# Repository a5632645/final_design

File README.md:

# final_design/毕业设计
This is my final design.  
这是我的本科毕业设计.  
> [!WARNING]
> don't try to rebuild hardware, it has too many incorrect design, that will just waste your time and money.  
> 请不要试着复刻硬件，有很多设计不合理的地方，复刻只会浪费你的时间和钱  

# digital waveguide synthesizer/数字波导合成器  
This is a MPE capability digital waveguide synthesizer.It has plucked, woodwind and bowed engine.Or you can use it as a MPE midi keyboard(only one octave).  
这是一个mpe兼容的数字波导合成器，有拨弦，木管和弓弦模型，也可以当成mpe键盘使用，尽管只有一个八度。  
# demo/演示
https://www.bilibili.com/video/BV1ghJGzJEi4/
# bug
硬件中含有较多问题  
the hardware has many bugs.

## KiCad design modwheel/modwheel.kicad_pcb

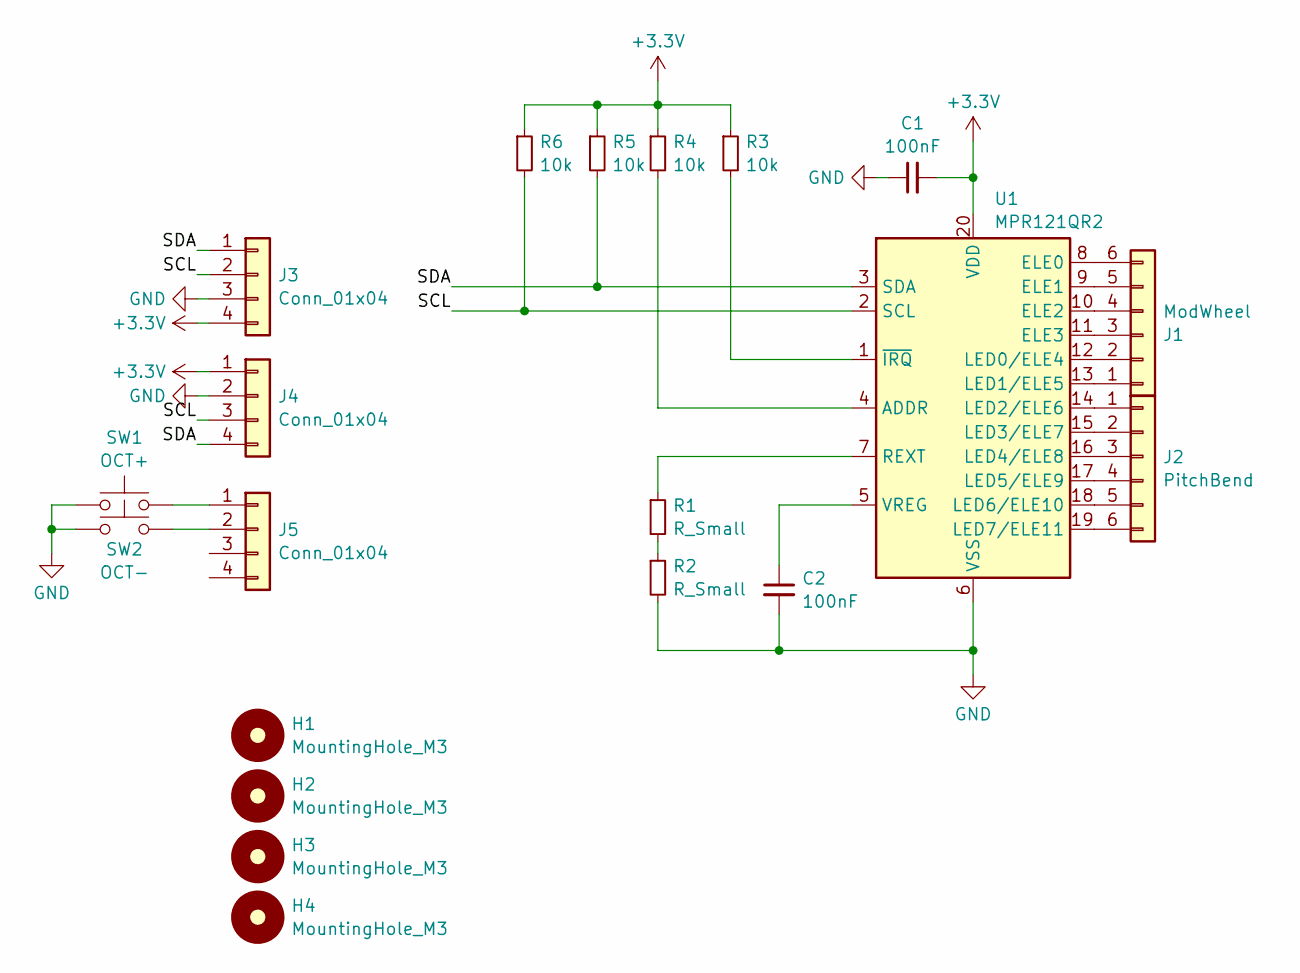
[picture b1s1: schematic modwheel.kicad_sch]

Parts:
C1, C2: 100nF; C_0603_1608Metric
H1, H2, H3, H4: MountingHole_M3; MountingHole_3.2mm_M3
J1: ModWheel; TouchSlider-6_50x10mm
J2: PitchBend; TouchSlider-6_50x10mm
J3, J4, J5: Conn_01x04; SM04BSRSSTB
R1, R2: R_Small; R_0603_1608Metric
R3, R4, R5, R6: 10k; R_0603_1608Metric
SW1: OCT+; KEY-SMD_2P-L6.0-W6.0-P6.00
SW2: OCT-; KEY-SMD_2P-L6.0-W6.0-P6.00
U1: MPR121QR2; UQFN-20_3x3mm_P0.4mm

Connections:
+3.3V: C1.2, J3.4, J4.1, R3.1, R4.1, R5.1, R6.1, U1.20 (VDD)
/SCL: J3.2, J4.3, R6.2, U1.2 (SCL)
/SDA: J3.1, J4.4, R5.2, U1.3 (SDA)
GND: C1.1, C2.2, J3.3, J4.2, R2.2, SW1.1, SW2.1, U1.6 (VSS)
unnamed: J1.1, U1.13 (LED1/ELE5)
unnamed: J1.2, U1.12 (LED0/ELE4)
unnamed: J1.3, U1.11 (ELE3)
unnamed: J1.4, U1.10 (ELE2)
unnamed: J1.5, U1.9 (ELE1)
unnamed: J1.6, U1.8 (ELE0)
unnamed: J2.1, U1.14 (LED2/ELE6)
unnamed: J2.2, U1.15 (LED3/ELE7)
unnamed: J2.3, U1.16 (LED4/ELE8)
unnamed: J2.4, U1.17 (LED5/ELE9)
unnamed: J2.5, U1.18 (LED6/ELE10)
unnamed: J2.6, U1.19 (LED7/ELE11)
unnamed: J5.1, SW1.2
unnamed: J5.2, SW2.2
unnamed: R1.2, R2.1
unnamed: R4.2, U1.4 (ADDR)
unnamed: R1.1, U1.7 (REXT)
unnamed: C2.1, U1.5 (VREG)
unnamed: R3.2, U1.1 (~IRQ)

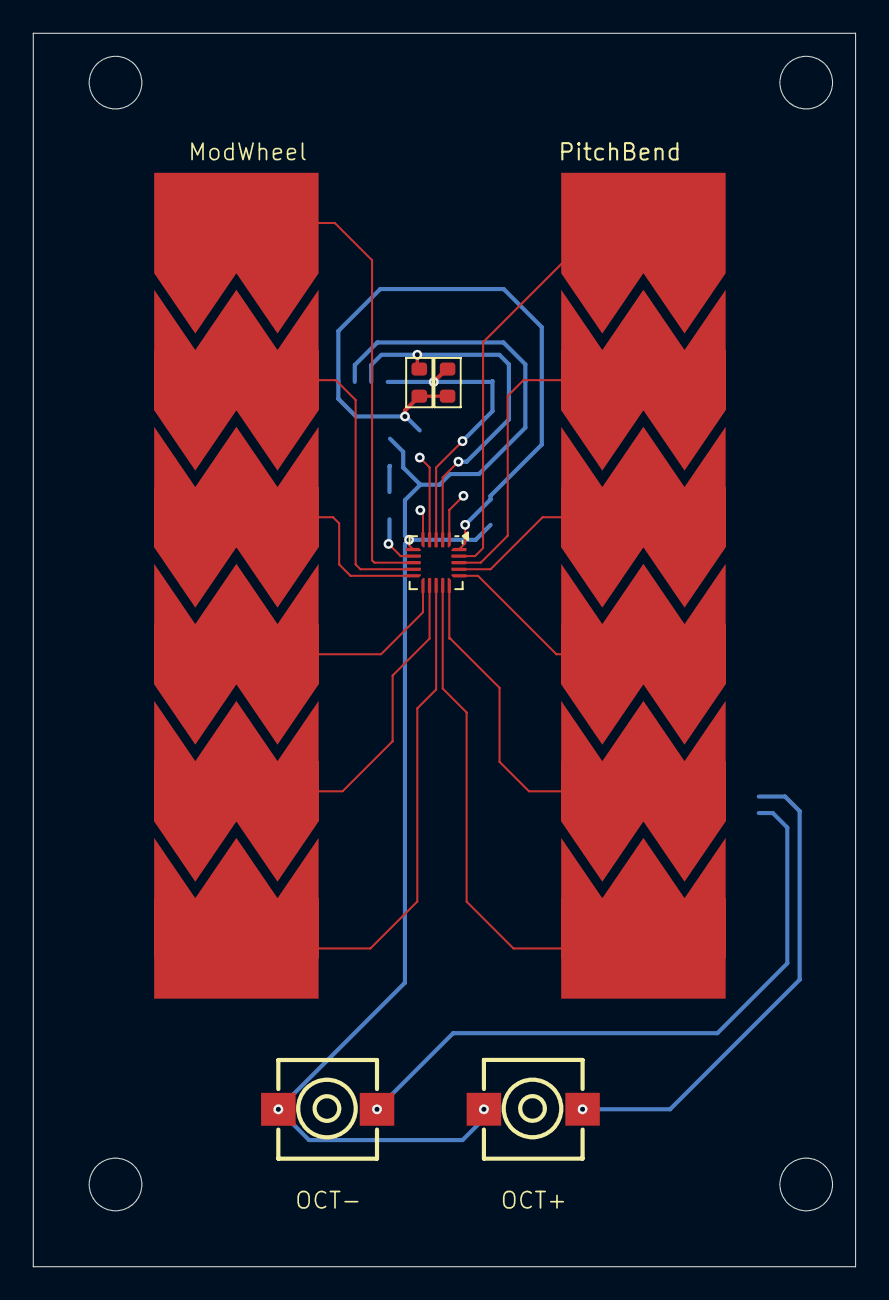
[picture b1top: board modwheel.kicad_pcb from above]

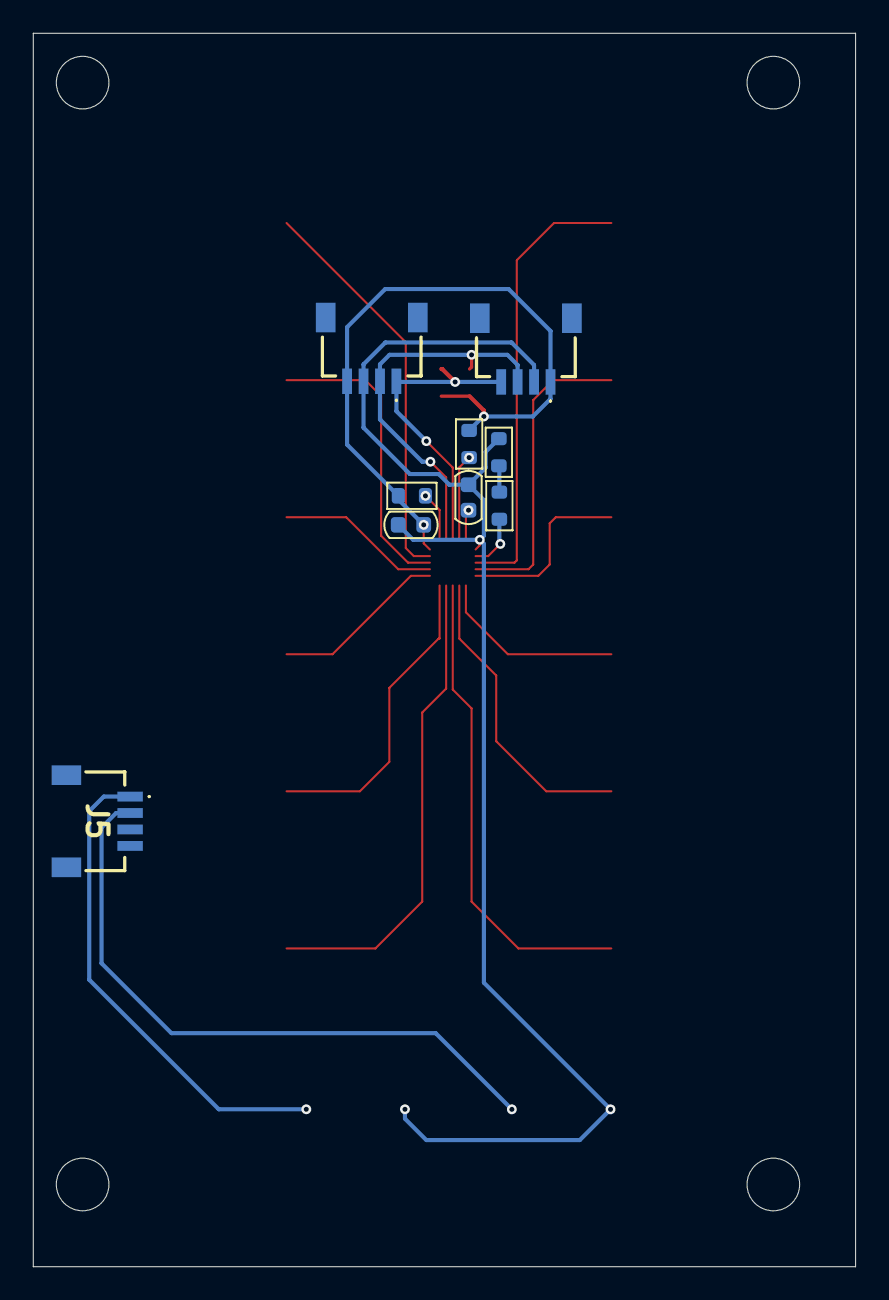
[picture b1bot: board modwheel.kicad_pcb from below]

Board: 2 copper layers, 50.0 x 75.0 mm, 20 parts (9 on the bottom side), 23 nets.

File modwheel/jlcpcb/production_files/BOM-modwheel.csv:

Comment,Designator,Footprint,LCSC,Quantity
Conn_01x04,J5,SM04BSRSSTB,,1
MPR121QR2,U1,UQFN-20_3x3mm_P0.4mm,,1
MountingHole_M3,H1,MountingHole_3.2mm_M3,,1
OCT+,SW1,KEY-SMD_2P-L6.0-W6.0-P6.00,,1
MountingHole_M3,H3,MountingHole_3.2mm_M3,,1
MountingHole_M3,H4,MountingHole_3.2mm_M3,,1
PitchBend,J2,TouchSlider-6_50x10mm,,1
ModWheel,J1,TouchSlider-6_50x10mm,,1
OCT-,SW2,KEY-SMD_2P-L6.0-W6.0-P6.00,,1
MountingHole_M3,H2,MountingHole_3.2mm_M3,,1
R_Small,R2,R_0603_1608Metric,,1
Conn_01x04,J3,SM04BSRSSTB,,1
R_Small,R1,R_0603_1608Metric,,1
100nF,C1,C_0603_1608Metric,,1
Conn_01x04,J4,SM04BSRSSTB,,1
100nF,C2,C_0603_1608Metric,,1
10k,R4,R_0603_1608Metric,,1
10k,R3,R_0603_1608Metric,,1
10k,R6,R_0603_1608Metric,,1
10k,R5,R_0603_1608Metric,,1

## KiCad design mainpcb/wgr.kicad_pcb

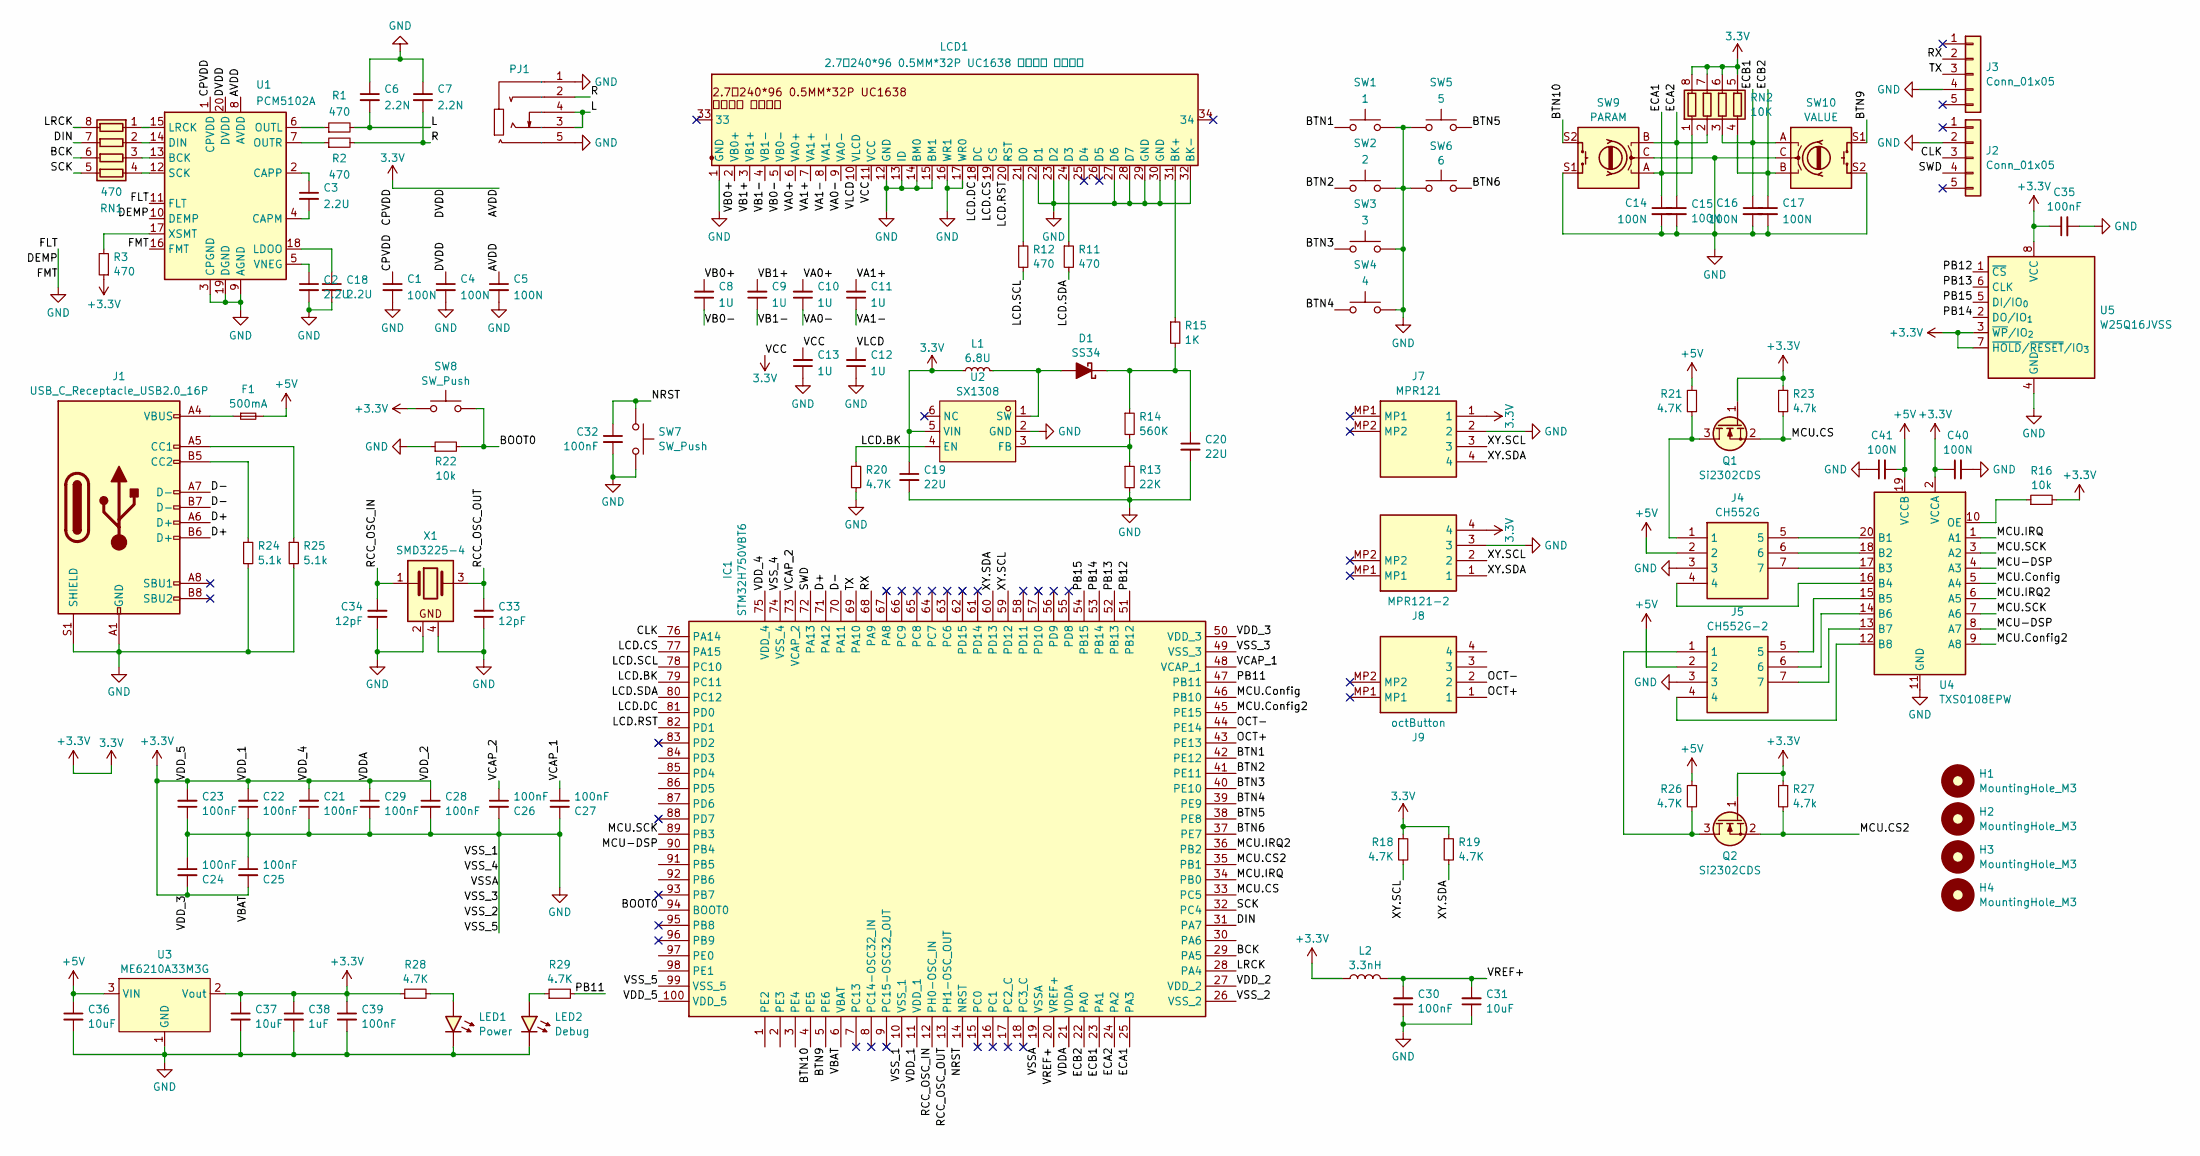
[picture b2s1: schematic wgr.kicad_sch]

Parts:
C1, C4, C5, C14, C15, C16, C17: 100N; C_0805_2012Metric
C2, C3, C18: 2.2U; C_0805_2012Metric
C6, C7: 2.2N; C_0805_2012Metric
C8, C9, C10, C11, C12, C13: 1U; C_0805_2012Metric
C19, C20: 22U; C_1206_3216Metric
C21, C22, C23, C24, C25, C26, C27, C28, C29, C30, C32, C35, C39: 100nF; C_0603_1608Metric
C31: 10uF; C_0603_1608Metric
C33, C34: 12pF; C_0603_1608Metric
C36, C37: 10uF; C_0805_2012Metric
C38: 1uF; C_0805_2012Metric
C40, C41: 100N; C_0603_1608Metric
D1: SS34; D_SMA
F1: 500mA; Fuse_0603_1608Metric
H1, H2, H3, H4: MountingHole_M3; MountingHole_3.2mm_M3
IC1: STM32H750VBT6; QFP50P1600X1600X160-100N; Manufacturer_Part_Number STM32H750VBT6; Mouser Part Number 511-STM32H750VBT6
J1: USB_C_Receptacle_USB2.0_16P; USB_C_Receptacle_G-Switch_GT-USB-7010ASV
J2, J3: Conn_01x05; Harwin_M20-89005xx_1x05_P2.54mm_Horizontal
J4: CH552G; SM07B-SRSS-TB; Manufacturer_Part_Number SM07B-SRSS-TB (LF)(SN)
J5: CH552G-2; SM07B-SRSS-TB; Manufacturer_Part_Number SM07B-SRSS-TB (LF)(SN)
J7: MPR121; SM04BSRSSTB; Manufacturer_Part_Number SM04B-SRSS-TB
J8: MPR121-2; SM04BSRSSTB; Manufacturer_Part_Number SM04B-SRSS-TB
J9: octButton; SM04BSRSSTB; Manufacturer_Part_Number SM04B-SRSS-TB
L1: 6.8U; L_APV_APH0420
L2: 3.3nH; L_0603_1608Metric; Part Number MI0603K300R-10
LCD1: 2.7寸240*96 0.5MM*32P UC1638 三串背光 背面插座; Hirose_FH12-32S-0.5SH_1x32-1MP_P0.50mm_Horizontal
LED1: Power; LED_0805_2012Metric
LED2: Debug; LED_0805_2012Metric
PJ1: AUDIO-IN-SMD_PJ-327A_C22355751; Manufacturer Part PJ-327A; LCSC Part Name PJ-327A
Q1, Q2: Si2302CDS; SOT-23
R1, R2, R3, R11, R12: 470; R_0805_2012Metric
R13: 22K; R_0603_1608Metric
R14: 560K; R_0603_1608Metric
R15: 1K; R_0805_2012Metric
R16: 10k; R_0603_1608Metric
R18, R19, R20, R21, R26, R28, R29: 4.7K; R_0805_2012Metric
R22: 10k; R_0603_1608Metric_Pad0.98x0.95mm
R23, R27: 4.7k; R_0805_2012Metric
R24, R25: 5.1k; R_0603_1608Metric_Pad0.98x0.95mm
RN1: 470; R_Array_Convex_4x0603
RN2: 10K; R_Array_Convex_4x0603
SW1: 1; KEY-SMD_2P-L6.0-W6.0-P6.00
SW2: 2; KEY-SMD_2P-L6.0-W6.0-P6.00
SW3: 3; KEY-SMD_2P-L6.0-W6.0-P6.00
SW4: 4; KEY-SMD_2P-L6.0-W6.0-P6.00
SW5: 5; KEY-SMD_2P-L6.0-W6.0-P6.00
SW6: 6; KEY-SMD_2P-L6.0-W6.0-P6.00
SW7, SW8: SW_Push; SW-SMD_4P-L4.5-W4.5-P3.00-LS7.0_TS-1009S-03826
SW9: PARAM; SW-TH_EC11XXXXXXXX
SW10: VALUE; SW-TH_EC11XXXXXXXX
U1: PCM5102A; TSSOP-20_4.4x6.5mm_P0.65mm
U2: SX1308; SOT-23-6_L2.9-W1.6-P0.95-LS2.8-BL; Manufacturer Part SX1308; LCSC Part Name 高效1.2MHz 2A升压转换器
U3: ME6210A33M3G; SOT-23
U4: TXS0108EPW; TSSOP-20_4.4x6.5mm_P0.65mm
U5: W25Q16JVSS; SOIC-8_5.3x5.3mm_P1.27mm
X1: SMD3225-4; Crystal_SMD_3225-4Pin_3.2x2.5mm

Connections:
+3.3V: C1.1, C4.1, C5.1, C13.2, C19.1, C21.2, C22.2, C23.2, C24.2, C25.2, C28.1, C29.1, C35.1, C37.1, C38.1, C39.1, C40.1, IC1.6 (VBAT), IC1.11 (VDD_1), IC1.21 (VDDA), IC1.27 (VDD_2), IC1.50 (VDD_3), IC1.75 (VDD_4), IC1.100 (VDD_5), J7.1, J8.4, L1.1, L2.1, LCD1.11 (VCC), Q1.1 (G), Q2.1 (G), R3.1, R16.2, R18.1, R19.1, R23.1, R27.1, R28.1, RN2.5 (R4.2), RN2.6 (R3.2), RN2.7 (R2.2), RN2.8 (R1.2), SW8.1, U1.1 (CPVDD), U1.8 (AVDD), U1.20 (DVDD), U2.5 (VIN), U3.2 (Vout), U4.2 (VCCA), U5.3 (~WP/IO_{2}), U5.7 (~HOLD/~RESET/IO_{3}), U5.8 (VCC)
+5V: C36.1, C41.2, F1.2, J4.2, J5.2, R21.1, R26.1, U3.3 (VIN), U4.19 (VCCB)
/BCK: IC1.29 (PA5), RN1.6 (R3.2)
/BOOT0: IC1.94 (BOOT0), R22.2, SW8.2
/BTN1: IC1.42 (PE12), SW1.1
/BTN2: IC1.41 (PE11), SW2.1
/BTN3: IC1.40 (PE10), SW3.1
/BTN4: IC1.39 (PE9), SW4.1
/BTN5: IC1.38 (PE8), SW5.2
/BTN6: IC1.37 (PE7), SW6.2
/BTN9: IC1.5 (PE6), SW10.S1
/BTN10: IC1.4 (PE5), SW9.S2
/CLK: IC1.76 (PA14), J2.3
/D+: IC1.71 (PA12), J1.A6 (D+), J1.B6 (D+)
/D-: IC1.70 (PA11), J1.A7 (D-), J1.B7 (D-)
/DIN: IC1.31 (PA7), RN1.7 (R2.2)
/ECA1: C14.1, IC1.25 (PA3), RN2.1 (R1.1), SW9.A
/ECA2: C15.1, IC1.24 (PA2), RN2.2 (R2.1), SW9.B
/ECB1: C16.1, IC1.23 (PA1), RN2.3 (R3.1), SW10.A
/ECB2: C17.1, IC1.22 (PA0), RN2.4 (R4.1), SW10.B
/L: C6.2, PJ1.3, PJ1.4, R1.2
/LCD.BK: IC1.79 (PC11), R20.1, U2.4 (EN)
/LCD.CS: IC1.77 (PA15), LCD1.19 (CS)
/LCD.DC: IC1.81 (PD0), LCD1.18 (DC)
/LCD.RST: IC1.82 (PD1), LCD1.20 (RST)
/LCD.SCL: IC1.78 (PC10), R12.2
/LCD.SDA: IC1.80 (PC12), R11.2
/LRCK: IC1.28 (PA4), RN1.8 (R1.2)
/MCU-DSP: IC1.90 (PB4), U4.4 (A3), U4.8 (A7)
/MCU.CS: IC1.33 (PC5), Q1.2 (S), R23.2
/MCU.CS2: IC1.35 (PB1), Q2.2 (S), R27.2
/MCU.Config: IC1.46 (PB10), U4.5 (A4)
/MCU.Config2: IC1.45 (PE15), U4.9 (A8)
/MCU.IRQ: IC1.34 (PB0), U4.1 (A1)
/MCU.IRQ2: IC1.36 (PB2), U4.6 (A5)
/MCU.SCK: IC1.89 (PB3), U4.3 (A2), U4.7 (A6)
/NRST: C32.1, IC1.14 (NRST), SW7.1
/OCT+: IC1.43 (PE13), J9.1
/OCT-: IC1.44 (PE14), J9.2
/PB12: IC1.51 (PB12), U5.1 (~CS)
/PB13: IC1.52 (PB13), U5.6 (CLK)
/PB14: IC1.53 (PB14), U5.2 (DO/IO_{1})
/PB15: IC1.54 (PB15), U5.5 (DI/IO_{0})
/R: C7.2, PJ1.2, R2.2
/RCC_OSC_IN: C34.2, IC1.12 (PH0-OSC_IN), X1.1
/RCC_OSC_OUT: C33.2, IC1.13 (PH1-OSC_OUT), X1.3
/RX: IC1.68 (PA9), J3.2
/SCK: IC1.32 (PC4), RN1.5 (R4.2)
/SWD: IC1.72 (PA13), J2.4
/TX: IC1.69 (PA10), J3.3
/VA0+: C10.2, LCD1.6 (VA0+)
/VA0-: C10.1, LCD1.9 (VA0-)
/VA1+: C11.2, LCD1.7 (VA1+)
/VA1-: C11.1, LCD1.8 (VA1-)
/VB0+: C8.2, LCD1.2 (VB0+)
/VB0-: C8.1, LCD1.5 (VB0-)
/VB1+: C9.2, LCD1.3 (VB1+)
/VB1-: C9.1, LCD1.4 (VB1-)
/VCAP_1: C27.1, IC1.48 (VCAP_1)
/VCAP_2: C26.1, IC1.73 (VCAP_2)
/VLCD: C12.2, LCD1.10 (VLCD)
/VREF+: C30.2, C31.2, IC1.20 (VREF+), L2.2
/XY.SCL: IC1.59 (PD12), J7.3, J8.2, R18.2
/XY.SDA: IC1.60 (PD13), J7.4, J8.1, R19.2
GND: C1.2, C2.2, C4.2, C5.2, C6.1, C7.1, C12.1, C13.1, C14.2, C15.2, C16.2, C17.2, C18.2, C19.2, C20.2, C21.1, C22.1, C23.1, C24.1, C25.1, C26.2, C27.2, C28.2, C29.2, C30.1, C31.1, C32.2, C33.1, C34.1, C35.2, C36.2, C37.2, C38.2, C39.2, C40.2, C41.1, IC1.10 (VSS_1), IC1.19 (VSSA), IC1.26 (VSS_2), IC1.49 (VSS_3), IC1.74 (VSS_4), IC1.99 (VSS_5), J1.A1 (GND), J1.A12 (GND), J1.B1 (GND), J1.B12 (GND), J1.S1 (SHIELD), J2.2, J3.4, J4.3, J5.3, J7.2, J8.3, LCD1.1 (GND), LCD1.12 (GND), LCD1.13 (ID), LCD1.14 (BM0), LCD1.15 (BM1), LCD1.16 (WR1), LCD1.17 (WR0), LCD1.22 (D1), LCD1.23 (D2), LCD1.27 (D6), LCD1.28 (D7), LCD1.29 (GND), LCD1.30 (GND), LCD1.32 (BK-), LED1.1 (K), LED2.1 (K), PJ1.1, PJ1.5, R13.2, R20.2, R22.1, R24.2, R25.2, SW1.2, SW2.2, SW3.2, SW4.2, SW5.1, SW6.1, SW7.2, SW9.C, SW9.S1, SW10.C, SW10.S2, U1.3 (CPGND), U1.9 (AGND), U1.10 (DEMP), U1.11 (FLT), U1.16 (FMT), U1.19 (DGND), U2.2 (GND), U3.1 (GND), U4.11 (GND), U5.4 (GND), X1.2, X1.4
unnamed: D1.2 (A), L1.2, U2.1 (SW)
unnamed: C20.1, D1.1 (K), R14.1, R15.2
unnamed: F1.1, J1.A4 (VBUS), J1.A9 (VBUS), J1.B4 (VBUS), J1.B9 (VBUS)
unnamed: IC1.47 (PB11), R29.2
unnamed: J1.A5 (CC1), R25.1
unnamed: J1.B5 (CC2), R24.1
unnamed: LCD1.31 (BK+), R15.1
unnamed: LCD1.21 (D0), R12.1
unnamed: LCD1.24 (D3), R11.1
unnamed: LED1.2 (A), R28.2
unnamed: LED2.2 (A), R29.1
unnamed: J4.1, Q1.3 (D), R21.2
unnamed: J5.1, Q2.3 (D), R26.2
unnamed: RN1.1 (R1.1), U1.15 (LRCK)
unnamed: RN1.2 (R2.1), U1.14 (DIN)
unnamed: RN1.3 (R3.1), U1.13 (BCK)
unnamed: RN1.4 (R4.1), U1.12 (SCK)
unnamed: C3.2, U1.4 (CAPM)
unnamed: C3.1, U1.2 (CAPP)
unnamed: C18.1, U1.18 (LDOO)
unnamed: R1.1, U1.6 (OUTL)
unnamed: R2.1, U1.7 (OUTR)
unnamed: C2.1, U1.5 (VNEG)
unnamed: R3.2, U1.17 (XSMT)
unnamed: R13.1, R14.2, U2.3 (FB)
unnamed: J4.5, U4.20 (B1)
unnamed: J4.6, U4.18 (B2)
unnamed: J4.7, U4.17 (B3)
unnamed: J4.4, U4.16 (B4)
unnamed: J5.5, U4.15 (B5)
unnamed: J5.6, U4.14 (B6)
unnamed: J5.7, U4.13 (B7)
unnamed: J5.4, U4.12 (B8)
unnamed: R16.1, U4.10 (OE)

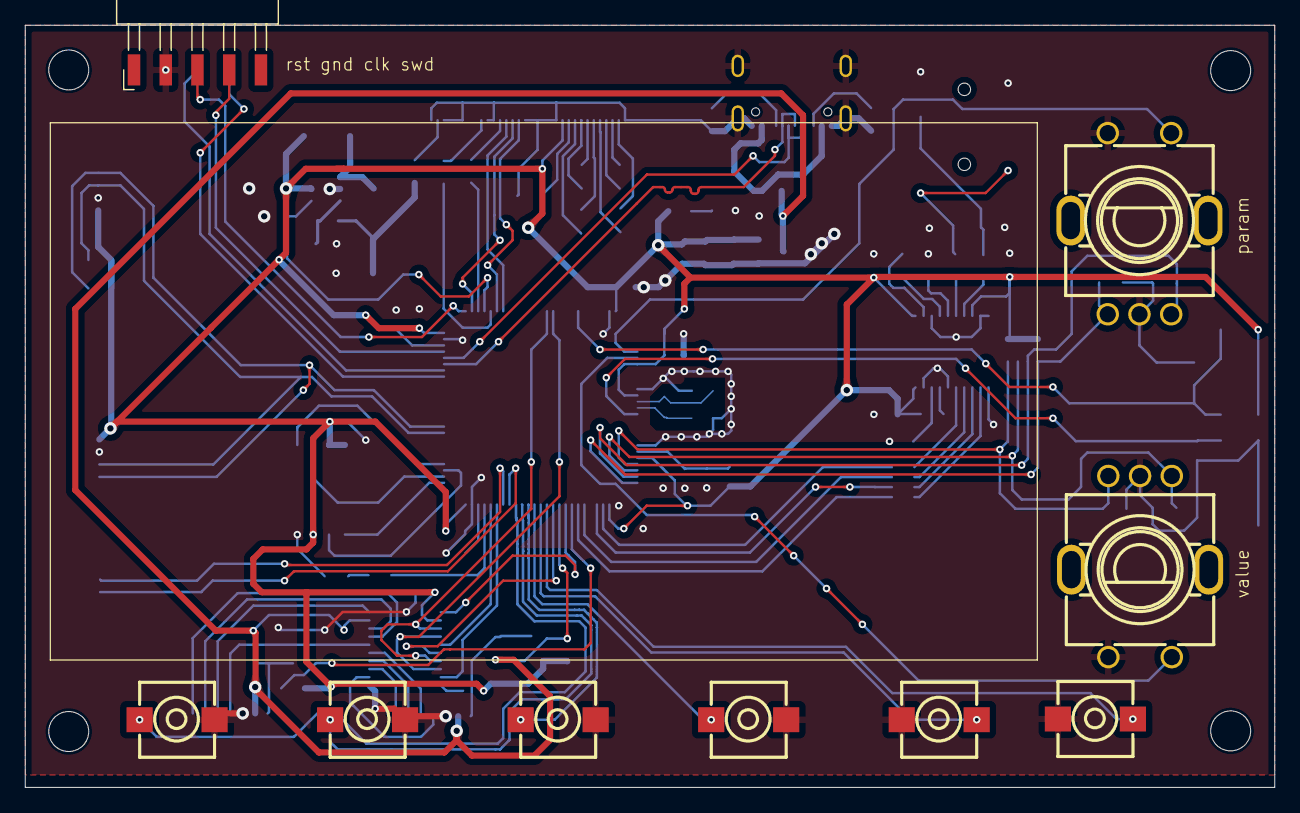
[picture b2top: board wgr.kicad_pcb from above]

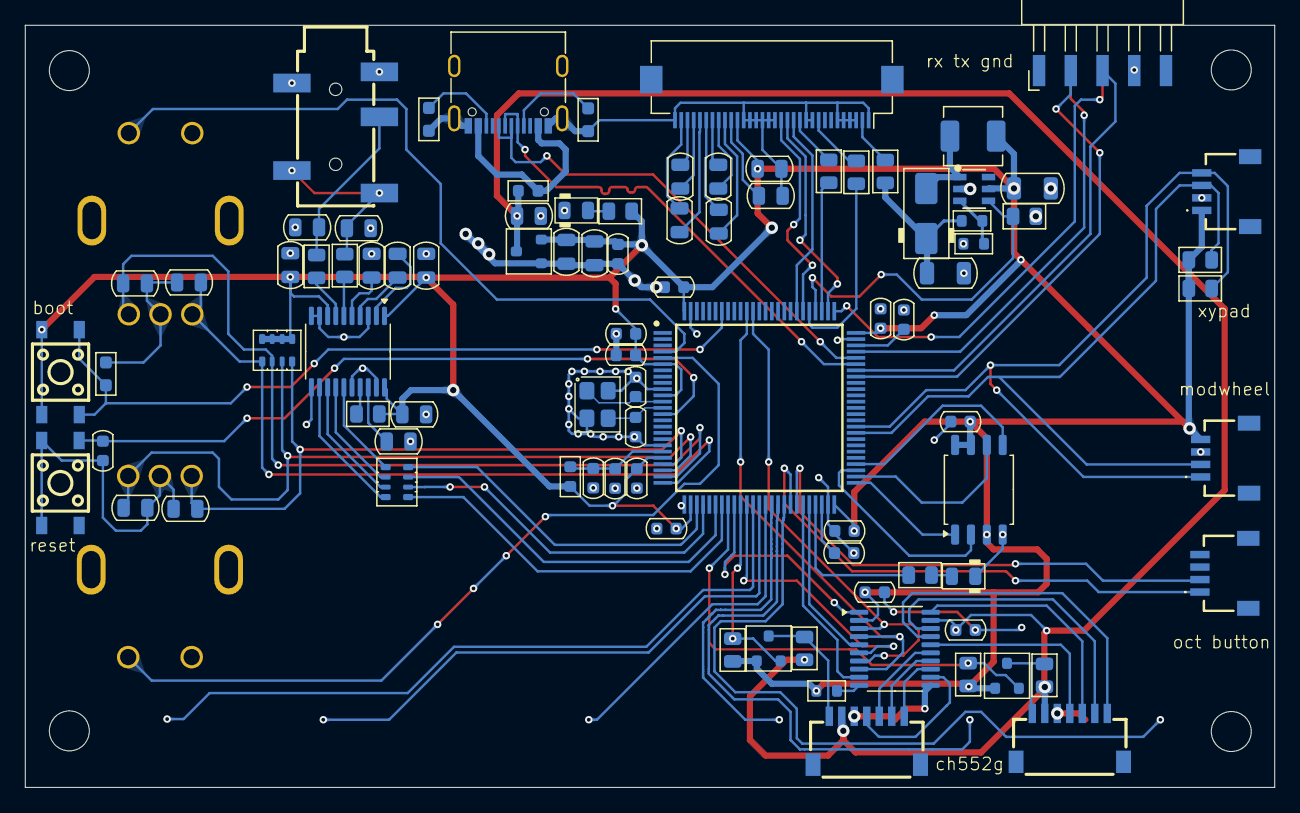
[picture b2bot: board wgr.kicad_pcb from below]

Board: 2 copper layers, 100.0 x 61.0 mm, 103 parts (90 on the bottom side), 99 nets.

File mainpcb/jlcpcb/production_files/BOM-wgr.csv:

Comment,Designator,Footprint,LCSC,Quantity
MountingHole_M3,H2,MountingHole_3.2mm_M3,,1
6,SW6,KEY-SMD_2P-L6.0-W6.0-P6.00,,1
PARAM,SW9,SW-TH_EC11XXXXXXXX,,1
MountingHole_M3,H4,MountingHole_3.2mm_M3,,1
1,SW1,KEY-SMD_2P-L6.0-W6.0-P6.00,,1
2,SW2,KEY-SMD_2P-L6.0-W6.0-P6.00,,1
3,SW3,KEY-SMD_2P-L6.0-W6.0-P6.00,,1
VALUE,SW10,SW-TH_EC11XXXXXXXX,,1
5,SW5,KEY-SMD_2P-L6.0-W6.0-P6.00,,1
MountingHole_M3,H3,MountingHole_3.2mm_M3,,1
4,SW4,KEY-SMD_2P-L6.0-W6.0-P6.00,,1
MountingHole_M3,H1,MountingHole_3.2mm_M3,,1
22K,R13,R_0603_1608Metric,,1
MPR121,J7,SM04BSRSSTB,,1
100N,C17,C_0805_2012Metric,,1
470,R12,R_0805_2012Metric,,1
4.7K,R20,R_0805_2012Metric,,1
470,R11,R_0805_2012Metric,,1
2.2U,C18,C_0805_2012Metric,,1
100N,C16,C_0805_2012Metric,,1
470,R2,R_0805_2012Metric,,1
470,R1,R_0805_2012Metric,,1
4.7K,R21,R_0805_2012Metric,,1
1U,C9,C_0805_2012Metric,,1
2.7寸240*96 0.5MM*32P UC1638 三串背光 背面插座,LCD1,Hirose_FH12-32S-0.5SH_1x32-1MP_P0.50mm_Horizontal,,1
2.2N,C6,C_0805_2012Metric,,1
22U,C19,C_1206_3216Metric,,1
470,RN1,R_Array_Convex_4x0603,,1
1U,C10,C_0805_2012Metric,,1
Si2302CDS,Q1,SOT-23,,1
1U,C11,C_0805_2012Metric,,1
100N,C15,C_0805_2012Metric,,1
~,PJ1,AUDIO-IN-SMD_PJ-327A_C22355751,,1
2.2N,C7,C_0805_2012Metric,,1
4.7k,R23,R_0805_2012Metric,,1
10K,RN2,R_Array_Convex_4x0603,,1
100N,C14,C_0805_2012Metric,,1
6.8U,L1,L_APV_APH0420,,1
CH552G,J4,SM07B-SRSS-TB,,1
1K,R15,R_0805_2012Metric,,1
100N,C4,C_0805_2012Metric,,1
22U,C20,C_1206_3216Metric,,1
1U,C8,C_0805_2012Metric,,1
4.7K,R18,R_0805_2012Metric,,1
2.2U,C3,C_0805_2012Metric,,1
SS34,D1,D_SMA,,1
1U,C12,C_0805_2012Metric,,1
1U,C13,C_0805_2012Metric,,1
2.2U,C2,C_0805_2012Metric,,1
100N,C1,C_0805_2012Metric,,1
PCM5102A,U1,TSSOP-20_4.4x6.5mm_P0.65mm,,1
560K,R14,R_0603_1608Metric,,1
100N,C5,C_0805_2012Metric,,1
4.7K,R19,R_0805_2012Metric,,1
SX1308,U2,SOT-23-6_L2.9-W1.6-P0.95-LS2.8-BL,,1
Conn_01x05,J2,Harwin_M20-89005xx_1x05_P2.54mm_Horizontal,,1
Conn_01x05,J3,Harwin_M20-89005xx_1x05_P2.54mm_Horizontal,,1
STM32H750VBT6,IC1,QFP50P1600X1600X160-100N,,1
USB_C_Receptacle_USB2.0_16P,J1,USB_C_Receptacle_G-Switch_GT-USB-7010ASV,,1
100nF,C23,C_0603_1608Metric,,1
100nF,C27,C_0603_1608Metric,,1
octButton,J9,SM04BSRSSTB,,1
ME6210A33M3G,U3,SOT-23,,1
100nF,C39,C_0603_1608Metric,,1
1uF,C38,C_0805_2012Metric,,1
10uF,C37,C_0805_2012Metric,,1
10uF,C36,C_0805_2012Metric,,1
SMD3225-4,X1,Crystal_SMD_3225-4Pin_3.2x2.5mm,,1
22pF,C34,C_0603_1608Metric,,1
22pF,C33,C_0603_1608Metric,,1
10k,R22,R_0603_1608Metric_Pad0.98x0.95mm,,1
100nF,C30,C_0603_1608Metric,,1
5.1k,R24,R_0603_1608Metric_Pad0.98x0.95mm,,1
10uF,C31,C_0603_1608Metric,,1
100nF,C24,C_0603_1608Metric,,1
W25Q16JVSS,U5,SOIC-8_5.3x5.3mm_P1.27mm,,1
100nF,C29,C_0603_1608Metric,,1
100nF,C28,C_0603_1608Metric,,1
100nF,C26,C_0603_1608Metric,,1
SW_Push,SW7,SW-SMD_4P-L4.5-W4.5-P3.00-LS7.0_TS-1009S-03826,,1
100nF,C25,C_0603_1608Metric,,1
100nF,C32,C_0603_1608Metric,,1
SW_Push,SW8,SW-SMD_4P-L4.5-W4.5-P3.00-LS7.0_TS-1009S-03826,,1
100nF,C35,C_0603_1608Metric,,1
100nF,C22,C_0603_1608Metric,,1
MPR121-2,J8,SM04BSRSSTB,,1
5.1k,R25,R_0603_1608Metric_Pad0.98x0.95mm,,1
100nF,C21,C_0603_1608Metric,,1
600R,L2,L_0603_1608Metric,,1
500mA,F1,Fuse_0603_1608Metric,,1
470,R3,R_0805_2012Metric,,1
100N,C40,C_0603_1608Metric,,1
100N,C41,C_0603_1608Metric,,1
TXS0108EPW,U4,TSSOP-20_4.4x6.5mm_P0.65mm,,1
4.7K,R29,R_0805_2012Metric,,1
4.7K,R28,R_0805_2012Metric,,1
4.7k,R27,R_0805_2012Metric,,1
4.7K,R26,R_0805_2012Metric,,1
10k,R16,R_0603_1608Metric,,1
Si2302CDS,Q2,SOT-23,,1
Debug,LED2,LED_0805_2012Metric,,1
Power,LED1,LED_0805_2012Metric,,1
CH552G-2,J5,SM07B-SRSS-TB,,1

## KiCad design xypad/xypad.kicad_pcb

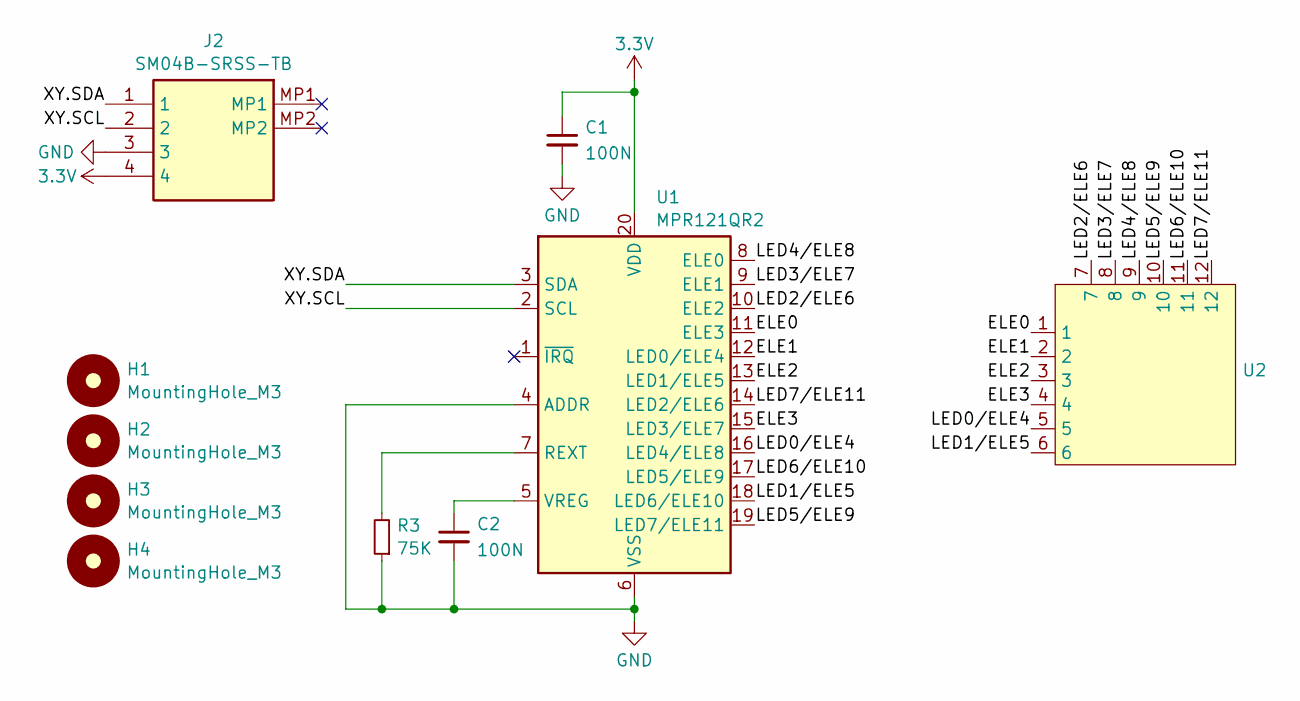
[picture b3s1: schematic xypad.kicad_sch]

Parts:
C1, C2: 100N; C_0805_2012Metric
H1, H2, H3, H4: MountingHole_M3; MountingHole_3.2mm_M3
J2: SM04B-SRSS-TB; SM04BSRSSTB; Manufacturer_Part_Number SM04B-SRSS-TB
R3: 75K; R_0805_2012Metric
U1: MPR121QR2; UQFN-20_3x3mm_P0.4mm
U2: touchpad6x6

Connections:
3.3V: C1.1, J2.4, U1.20 (VDD)
/ELE0: U1.11 (ELE3), U2.1
/ELE1: U1.12 (LED0/ELE4), U2.2
/ELE2: U1.13 (LED1/ELE5), U2.3
/ELE3: U1.15 (LED3/ELE7), U2.4
/LED0/ELE4: U1.16 (LED4/ELE8), U2.5
/LED1/ELE5: U1.18 (LED6/ELE10), U2.6
/LED2/ELE6: U1.10 (ELE2), U2.7
/LED3/ELE7: U1.9 (ELE1), U2.8
/LED4/ELE8: U1.8 (ELE0), U2.9
/LED5/ELE9: U1.19 (LED7/ELE11), U2.10
/LED6/ELE10: U1.17 (LED5/ELE9), U2.11
/LED7/ELE11: U1.14 (LED2/ELE6), U2.12
/XY.SCL: J2.2, U1.2 (SCL)
/XY.SDA: J2.1, U1.3 (SDA)
GND: C1.2, C2.2, J2.3, R3.1, U1.4 (ADDR), U1.6 (VSS)
unnamed: R3.2, U1.7 (REXT)
unnamed: C2.1, U1.5 (VREG)

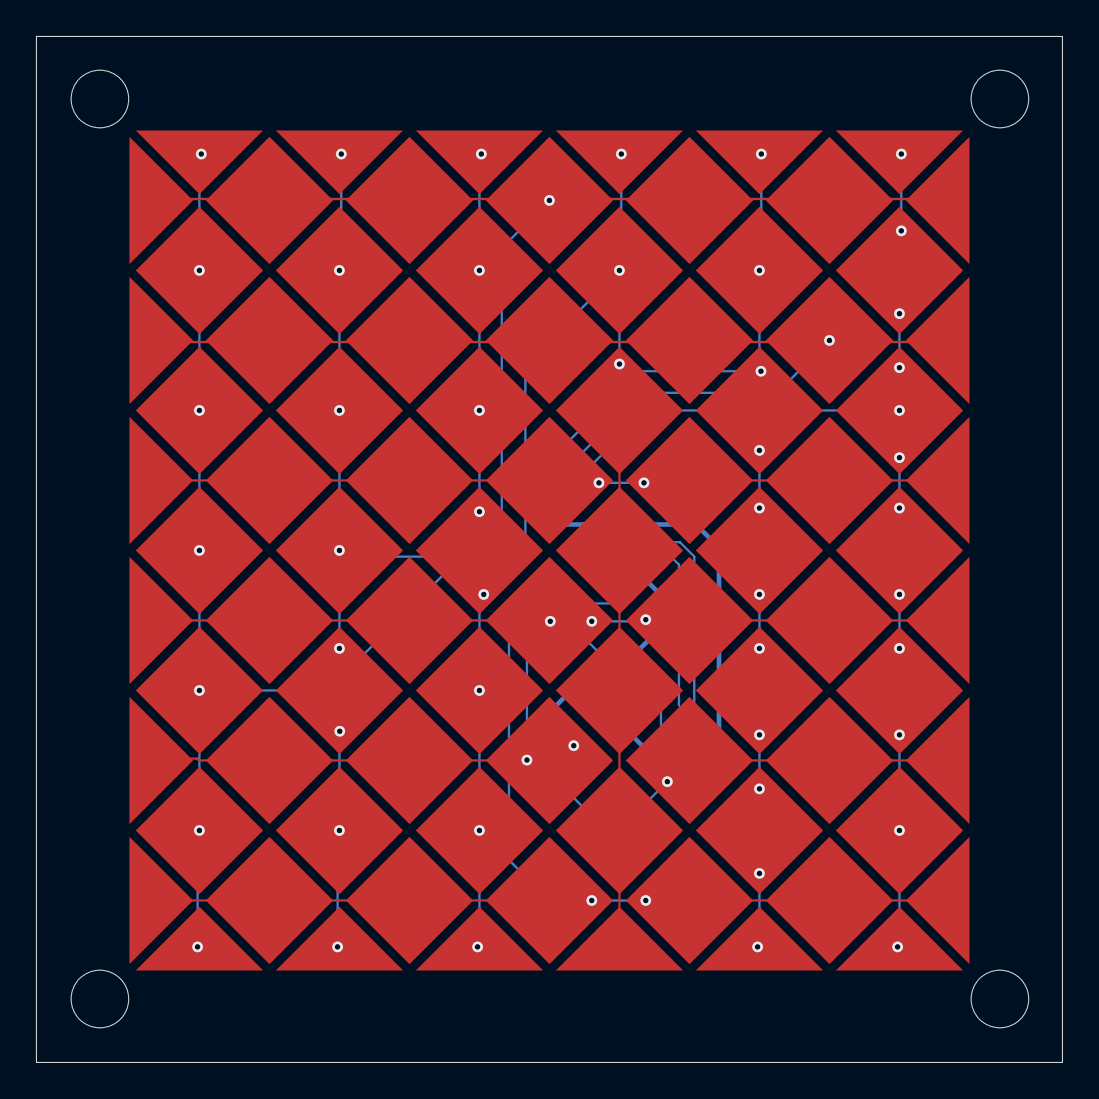
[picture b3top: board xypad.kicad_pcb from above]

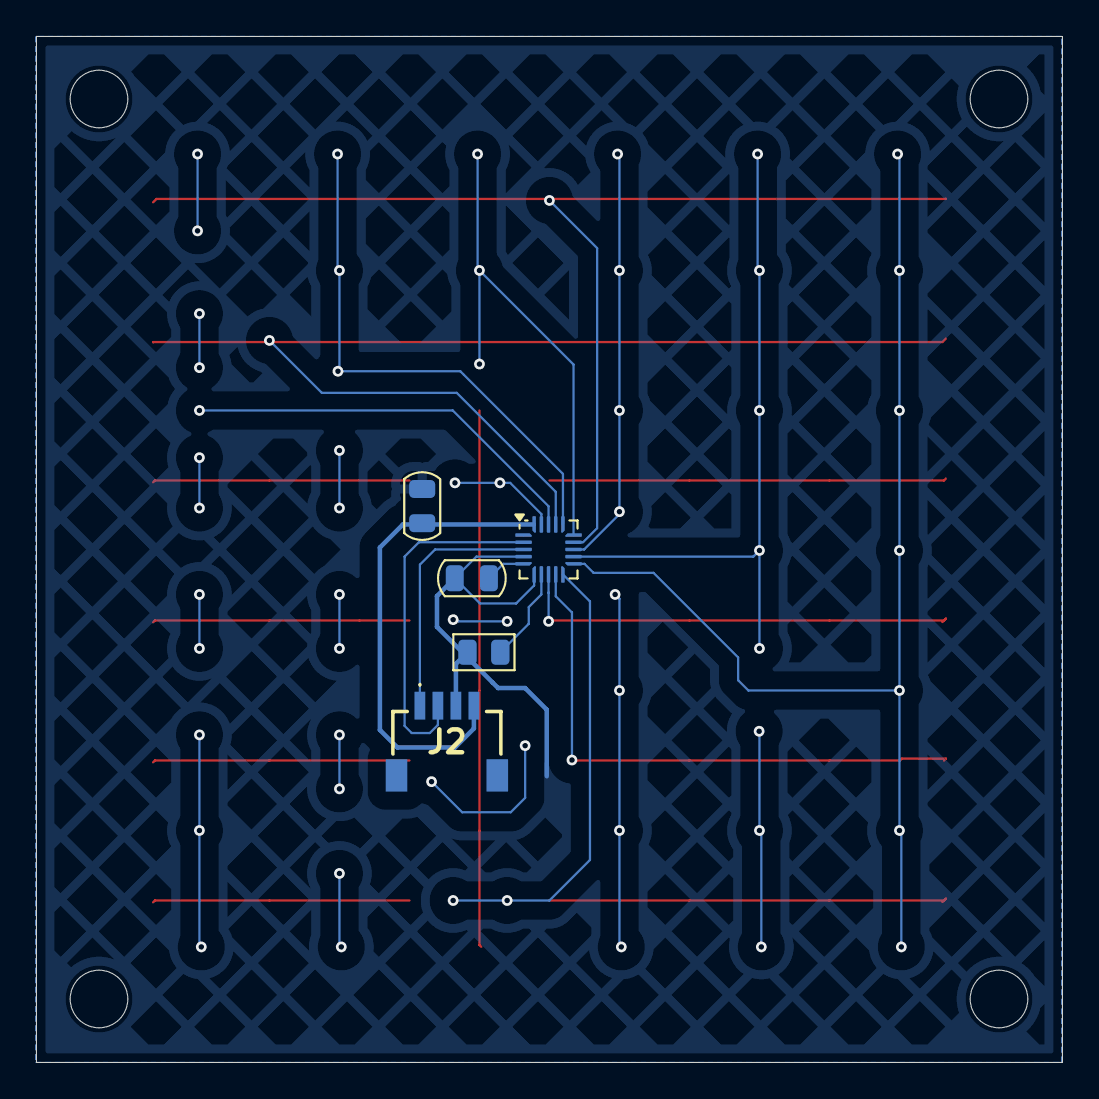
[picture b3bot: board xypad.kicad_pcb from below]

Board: 2 copper layers, 57.0 x 57.0 mm, 10 parts (5 on the bottom side), 18 nets.

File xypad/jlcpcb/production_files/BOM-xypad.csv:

Comment,Designator,Footprint,LCSC,Quantity
~,U2,touchpad6x6,,1
MountingHole_M3,H4,MountingHole_3.2mm_M3,,1
MountingHole_M3,H3,MountingHole_3.2mm_M3,,1
MountingHole_M3,H2,MountingHole_3.2mm_M3,,1
MountingHole_M3,H1,MountingHole_3.2mm_M3,,1
75K,R3,R_0805_2012Metric,,1
SM04B-SRSS-TB,J2,SM04BSRSSTB,,1
MPR121QR2,U1,UQFN-20_3x3mm_P0.4mm,,1
100N,C2,C_0805_2012Metric,,1
100N,C1,C_0805_2012Metric,,1

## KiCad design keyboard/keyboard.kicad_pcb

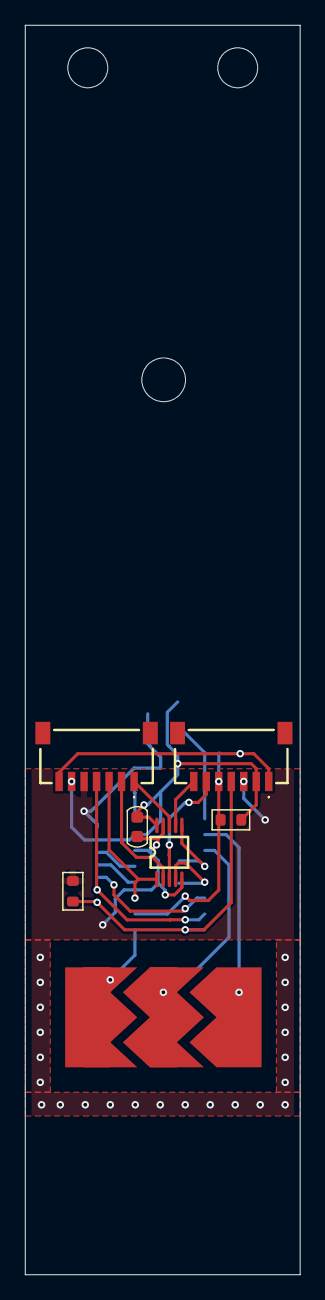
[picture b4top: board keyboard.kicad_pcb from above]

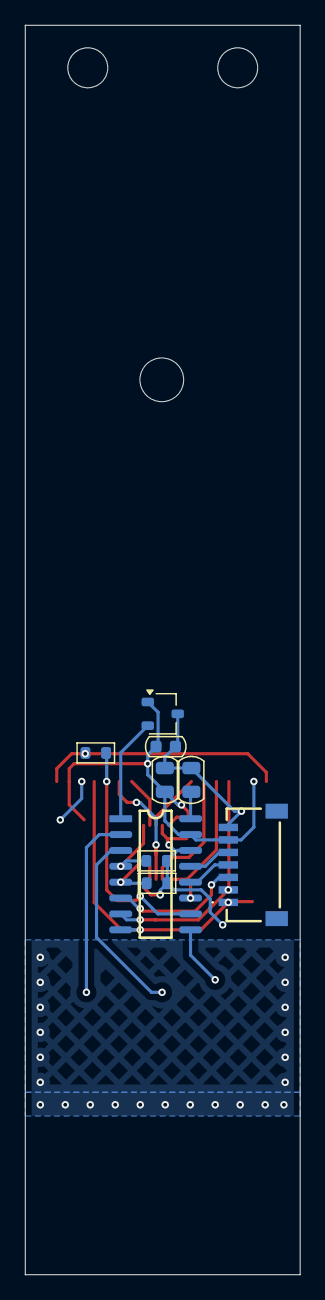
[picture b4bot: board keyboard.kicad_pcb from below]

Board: 2 copper layers, 22.0 x 100.0 mm, 19 parts (9 on the bottom side), 21 nets.

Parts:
C1, C2: 1U; C_0805_2012Metric
C3, C4: 100N; C_0603_1608Metric
H1, H2: FIXED; MountingHole_3.2mm_M3
H3: SPRING; MountingHole_3.2mm_M3
J1: PROGRAM; SM07BSRSSTBLFSN
J2: NEXT; SM07BSRSSTBLFSN
J3: PREV; SM07BSRSSTBLFSN
R1, R2, R3, R4: 4.7K; R_0603_1608Metric
R5: 0; R_0603_1608Metric
U1: OH49E; SOT-23W
U2: TouchSlider-3_16x8mm
U3: CH442E; MSOP10
U4: CH552G; SOP16

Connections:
5V: C2.1, C3.1, C4.1, J1.6, J2.6, J3.2, R1.1, U1.1 (VCC), U3.10 (VCC), U4.15 (VCC/VDD)
/AIN: U1.2 (VOUT), U4.1 (P3.2/TXD1_/INT0/VBUS1/AIN3)
/CS_NEXT: J2.3, U3.1 (IN), U4.11 (P3.4/PWM2/RXD1_/T0)
/CS_PREV: J3.5, R1.2, R5.2, U4.10 (P3.3/INT1)
/DM: J1.5, U4.13 (P3.7/UDM)
/DP: J1.4, U4.12 (P3.6/UDP)
/MCS: J2.7, J3.1, R5.1
/OK_NEXT: J1.2, J2.4, U4.7 (P3.1/PWM2_/TXD)
/OK_PREV: J1.1, J3.4, R2.1, U4.8 (P3.0/PWM1_/RXD)
/RESET: J1.3, U4.6 (RST/T2EX_/CAP2_)
/SCK: R4.1, U3.4 (DB), U4.5 (P1.7/SCK/TXD1/TIN5)
/SCK_NEXT: J2.2, U3.2 (S1B)
/SCK_PREV: J3.6, U3.3 (S2B)
/SDA: R3.1, U3.6 (DC), U4.4 (P1.6/MISO/RXD1/TIN4)
/SDA_NEXT: J2.1, U3.8 (S1C)
/SDA_PREV: J3.7, U3.7 (S2C)
/TIN0: U2.1, U4.9 (P1.1/T2EX/CAP2/TIN1/VBUS2/AIN0)
/TIN1: U2.3, U4.2 (P1.4/T2_/CAP1_/SCS/TIN2/UCC1/AIN1)
/TIN2: U2.2, U4.3 (P1.5/MOSI/PWM1/TIN3/UCC2/AIN2)
GND: C1.2, C2.2, C3.2, C4.2, J1.7, J2.5, J3.3, R2.2, R3.2, R4.2, U1.3 (GND), U3.5 (GND), U3.9 (EN#), U4.14 (GND/VSS)
unnamed: C1.1, U4.16 (V33)
